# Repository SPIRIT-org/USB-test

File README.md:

# This is a sub-project to test the USB 3.1 circuit.

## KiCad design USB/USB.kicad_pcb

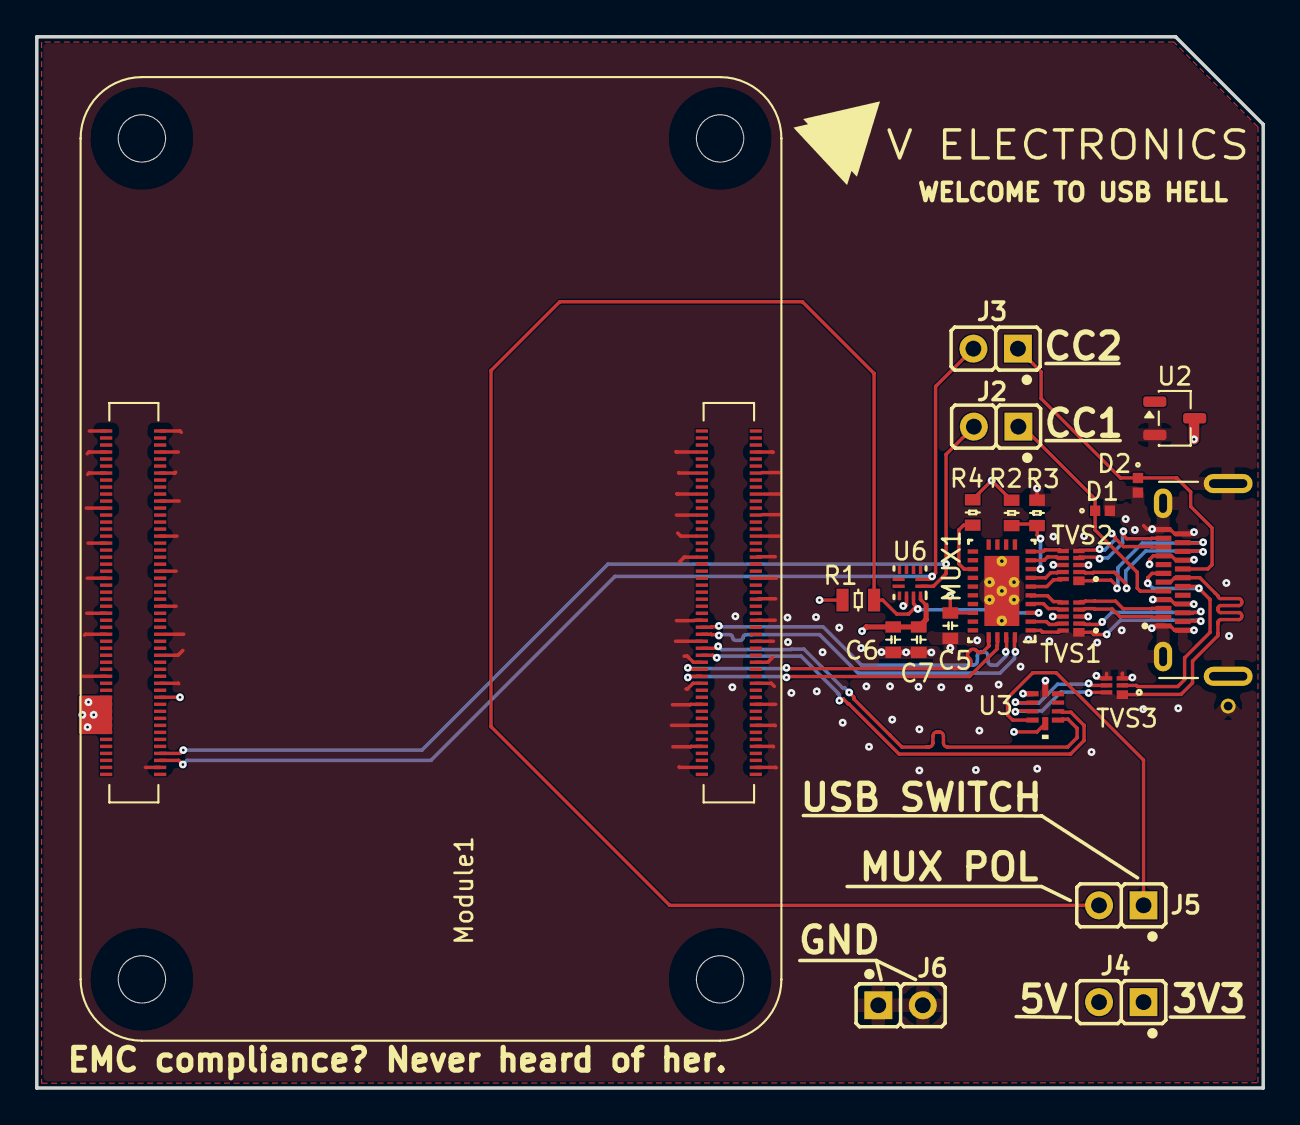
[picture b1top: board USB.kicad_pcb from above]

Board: 4 copper layers, 70.0 x 60.0 mm, 23 parts (0 on the bottom side), 40 nets.

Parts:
C5: 0.1uF; 0603-capacitor
C6: 100nF; 0603-capacitor
C7: 22uF; 0603-capacitor
D1, D2: TPD1E05U06DPYR; TPD1E05U-SON65P60X100X45-2N
J1: USBC-4-0-CX90MW9-24P1; USB-4-0-HIROSE_CX90MW9-24P1
J2, J3, J4, J5, J6: COMATEL_385.0358.1.02.400
MUX1: MUX HD3SS460RHRR; USB-MUX-RHR0028A
Module1: ComputeModule5-CM5; Raspberry-Pi-5-Compute-Module
R1: 1K-05W-0805; 0805-resistor
R2, R3, R4: 10kΩ; 0603-resistor
TVS1, TVS2: TVS-choke-2-pair-EMI8142MUTAG; 2-channel-TVS-chokeXDFN10_2P2X1P3_ONS
TVS3: 2 Line Common Mode Choke with ESD 100mA DCR 6Ohm; 1-channel-TVS-choke-XDFN6_1P2X1P2_ONS
U2: ESDA25L; SOT-23-3
U3: USB SWITCH 2CHANNEL TS3USB221AQRSERQ1; USB-SWITCH-2CHANNEL-TS3USB221AQRSERQ1
U6: usb-polarity-TUSB321RWBR; polarity-usb-TUSB321RWBR

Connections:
3V3B: C5.1, J4.1, MUX1.22 (VCC), Module1.78 (GPIO_VREF(1.8v/3.3v_Input)), R1.2, R2.2, R4.2, U3.10 (VCC)
5V: C6.1, C7.1, J4.2, Module1.77 (+5v_(Input)), Module1.79 (+5v_(Input)), Module1.81 (+5v_(Input)), Module1.83 (+5v_(Input)), Module1.85 (+5v_(Input)), Module1.87 (+5v_(Input)), U6.12 (VDD)
CC1: D1.1, J1.A5 (CC1), J2.1
CC1-jumpered: J2.2, Module1.94 (CC1), U6.1 (CC1)
CC2: D2.1, J1.B5 (CC2), J3.1
CC2-jumpered: J3.2, Module1.96 (CC2), U6.2 (CC2)
D+: J1.A6 (D1+), J1.B6 (D2+), TVS3.1 (D+IN)
D-: J1.A7 (D1-), J1.B7 (D2-), TVS3.2 (D-IN)
DSI1_D2_N: Module1.133 (MIPI0_D2_N), Module1.193 (MIPI1_D2_N)
DSI1_D2_P: Module1.135 (MIPI0_D2_P), Module1.195 (MIPI1_D2_P)
Df+: TVS3.6 (D+OUT), U3.8 (D+)
Df-: TVS3.5 (D-OUT), U3.7 (D-)
GND: C5.2, C6.2, C7.2, D1.2, D2.2, J1.A1 (GND_A), J1.A12 (GND_A__1), J1.B1 (GND_B), J1.B12 (GND_B__1), J1.SH1 (SHIELD), J1.SH2 (SHIELD__1), J1.SH3 (SHIELD__2), J1.SH4 (SHIELD__3), J6.1, J6.2, MUX1.29 (PAD_GND), Module1.1 (GND), Module1.2 (GND), Module1.7 (GND), Module1.8 (GND), Module1.13 (GND), Module1.14 (GND), Module1.22 (GND), Module1.23 (GND), Module1.32 (GND), Module1.33 (GND), Module1.42 (GND), Module1.43 (GND), Module1.52 (GND), Module1.53 (GND), Module1.59 (GND), Module1.60 (GND), Module1.66 (GND), Module1.71 (GND), Module1.74 (GND), Module1.98 (GND), Module1.107 (GND), Module1.108 (GND), Module1.113 (GND), Module1.114 (GND), Module1.119 (GND), Module1.120 (GND), Module1.125 (GND), Module1.126 (GND), Module1.131 (GND), Module1.132 (GND), Module1.137 (GND), Module1.138 (GND), Module1.144 (GND), Module1.150 (GND), Module1.155 (GND), Module1.156 (GND), Module1.161 (GND), Module1.162 (GND), Module1.167 (GND), Module1.168 (GND), Module1.173 (GND), Module1.174 (GND), Module1.179 (GND), Module1.180 (GND), Module1.185 (GND), Module1.186 (GND), Module1.191 (GND), Module1.192 (GND), Module1.197 (GND), Module1.198 (GND), R3.2, TVS1.3 (GND), TVS1.8 (GND), TVS2.3 (GND), TVS2.8 (GND), TVS3.3 (GND), TVS3.4 (GND), U2.2, U3.5 (GND), U3.6 (~OE), U6.10 (GND)
MUX POL: J5.2, MUX1.3 (POL), R1.1, U6.11 (DIR)
unnamed: MUX1.8 (AMSEL), R2.1, R3.1
unnamed: MUX1.17 (EN), R4.1
RX1+: J1.B11 (RX1+), TVS1.1 (IN_1+)
RX1-: J1.B10 (RX1-), TVS1.2 (IN_1−)
RX1f+: MUX1.1 (CRX1P), TVS1.10 (OUT_1+)
RX1f-: MUX1.2 (CRX1N), TVS1.9 (OUT_1-)
RX2+: J1.A11 (RX2+), TVS2.4 (IN_2+)
RX2-: J1.A10 (RX2-), TVS2.5 (IN_2-)
RX2f+: MUX1.9 (CRX2P), TVS2.7 (OUT_2+)
RX2f-: MUX1.10 (CRX2N), TVS2.6 (OUT_2-)
SSTR2+: MUX1.28 (SSRXP), Module1.159 (USB3-1-RX_P)
SSTR2-: MUX1.27 (SSRXN), Module1.157 (USB3-1-RX_N)
SSTX2+: MUX1.26 (SSTXP), Module1.171 (USB3-1-TX_P)
SSTX2-: MUX1.25 (SSTXN), Module1.169 (USB3-1-TX_N)
SYS D+: Module1.163 (USB3-1-D_P), U3.1 (1D+)
SYS D-: Module1.165 (USB3-1-D_N), U3.2 (1D-)
TX1+: J1.A2 (TX1+), TVS1.4 (IN_2+)
TX1-: J1.A3 (TX1-), TVS1.5 (IN_2-)
TX1f+: MUX1.4 (CTX1P), TVS1.7 (OUT_2+)
TX1f-: MUX1.5 (CTX1N), TVS1.6 (OUT_2-)
TX2+: J1.B2 (TX2+), TVS2.1 (IN_1+)
TX2-: J1.B3 (TX2-), TVS2.2 (IN_1−)
TX2f+: MUX1.6 (CTX2P), TVS2.10 (OUT_1+)
TX2f-: MUX1.7 (CTX2N), TVS2.9 (OUT_1-)
USB SWITCH: J5.1, U3.9 (S)
USBC POW: J1.A4 (VBUS_A), J1.A9 (VBUS_A__1), J1.B4 (VBUS_B), J1.B9 (VBUS_B__1), U2.3
